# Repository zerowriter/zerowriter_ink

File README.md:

# zerowriter_ink

General repo for all things Zerowriter Ink.

Note that the current public firmware is 1.1. If you are using a factory Zerowriter Ink, you may experience some bugs.

For those field testing or using new units, consider opening an issue if you find bugs. You can do that here: (https://github.com/zerowriter/zerowriter_ink/issues)

This repo will be updated with the source code, documentation, and design files for ZW Ink.

Also consider sharing your custom fonts (.bbf), layouts (layout.json), and other tools you may find helpful.

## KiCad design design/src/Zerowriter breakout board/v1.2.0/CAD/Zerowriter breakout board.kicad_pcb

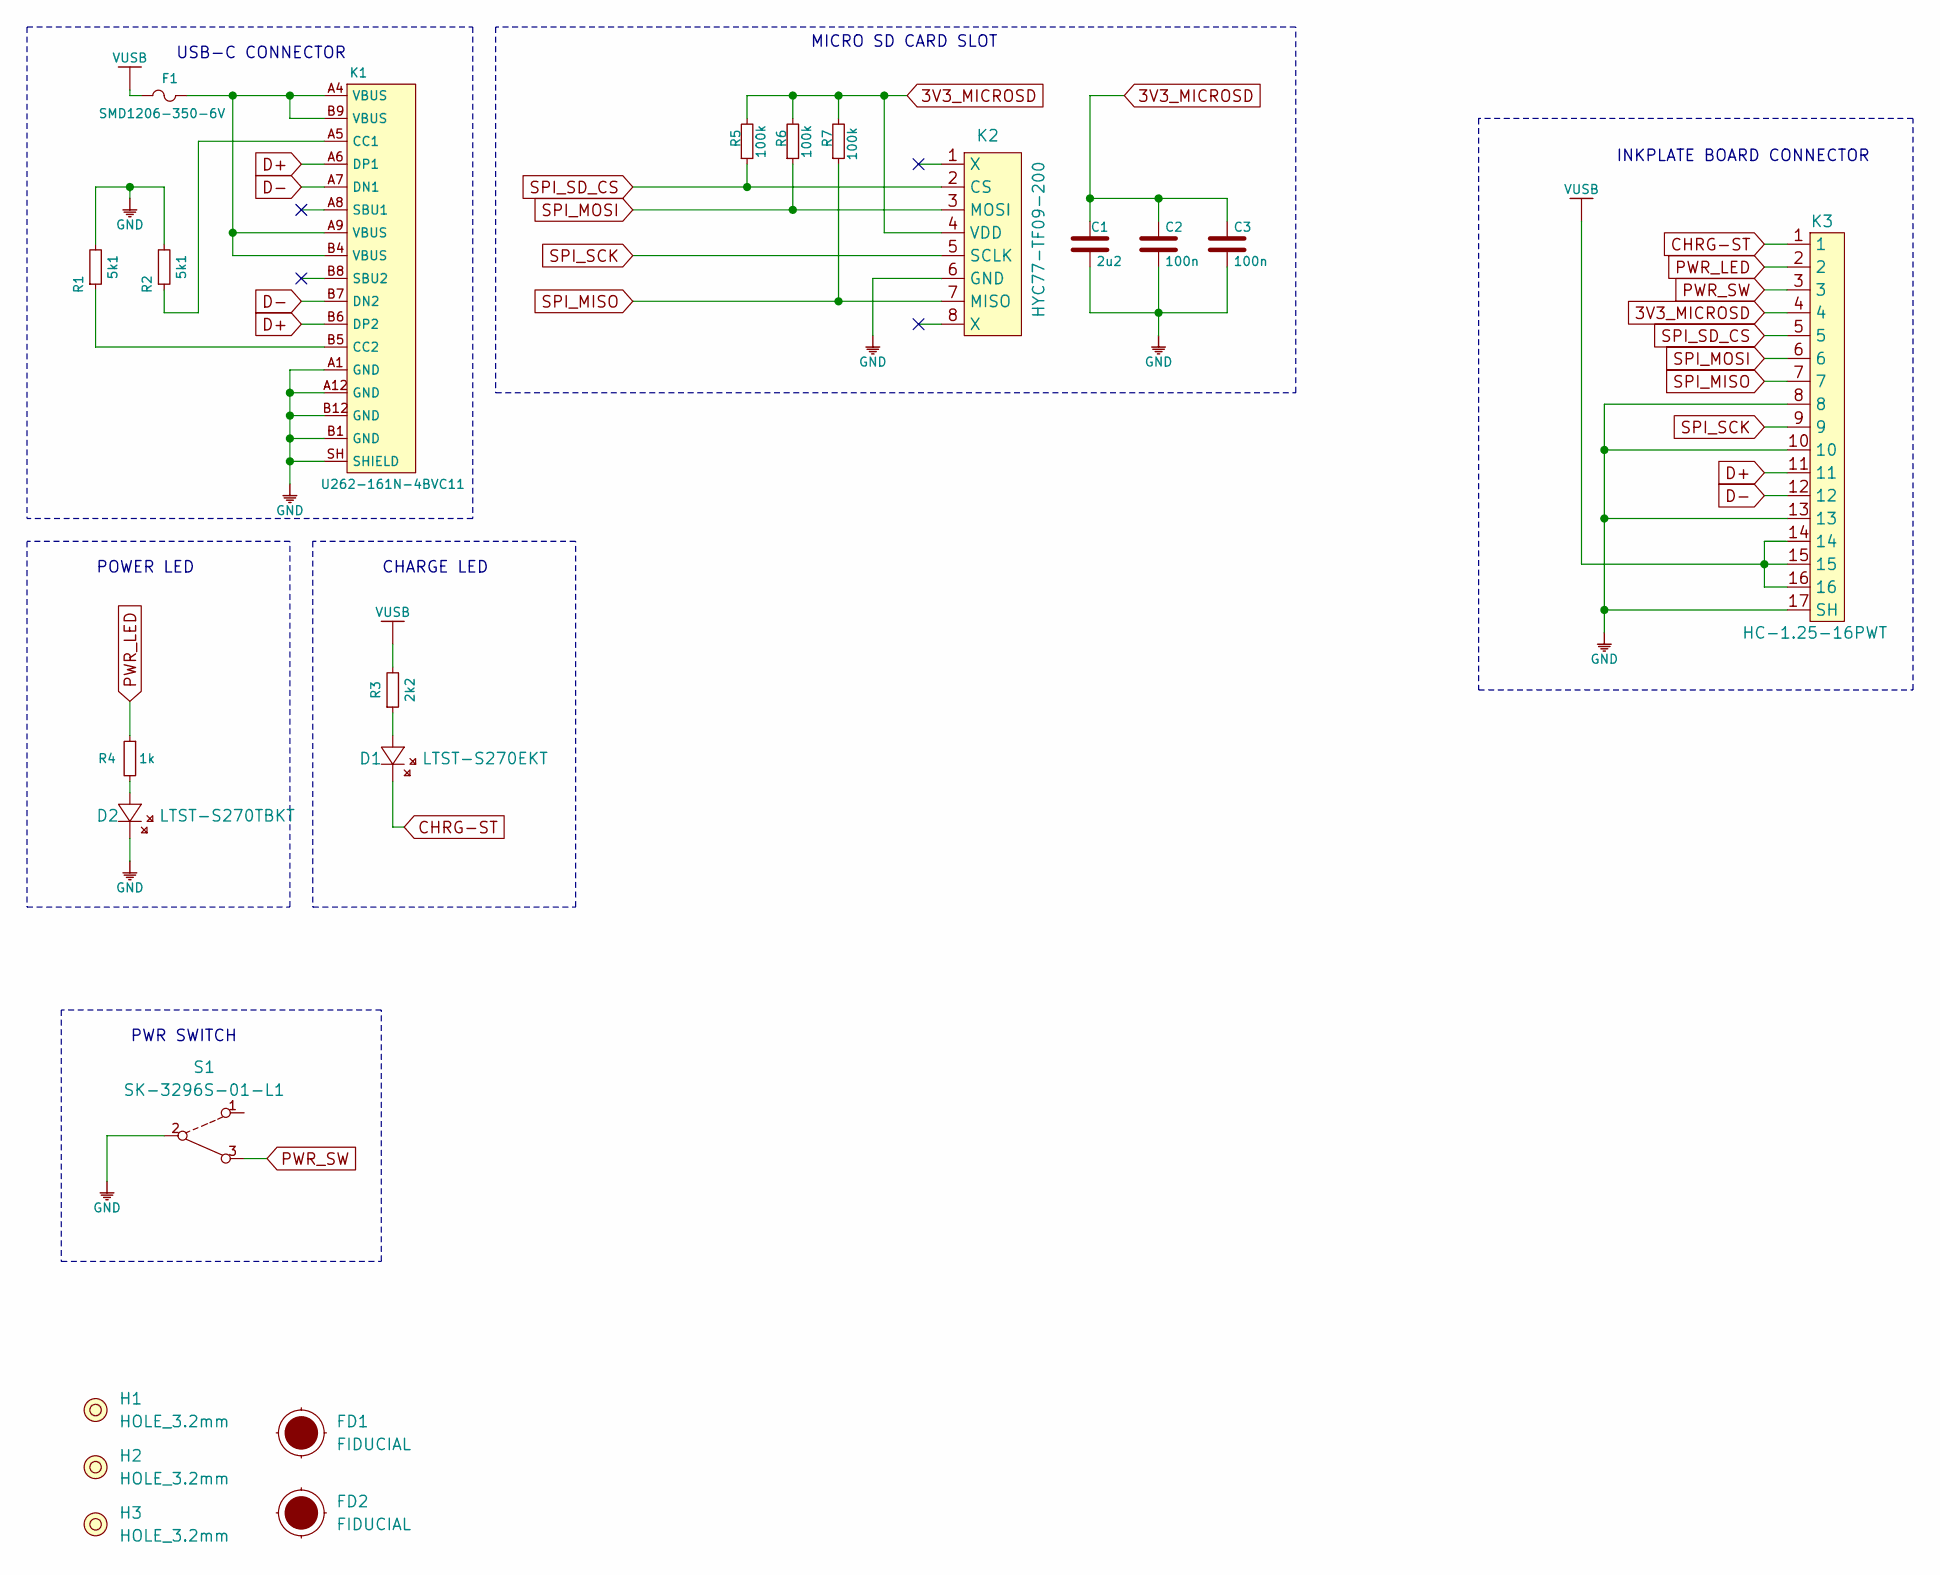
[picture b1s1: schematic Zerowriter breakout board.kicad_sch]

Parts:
C1: 2u2; 0603C
C2, C3: 100n; 0603C
D1: LTST-S270EKT; LTST-S270GKT
D2: LTST-S270TBKT; LTST-S270GKT
F1: SMD1206-350-6V; 1206FUSE
FD1, FD2: FIDUCIAL
H1, H2, H3: HOLE_3.2mm
K1: U262-161N-4BVC11
K2: HYC77-TF09-200
K3: HC-1.25-16PWT
R1, R2: 5k1; 0603R
R3: 2k2; 0603R
R4: 1k; 0603R
R5, R6, R7: 100k; 0603R
S1: SK-3296S-01-L1

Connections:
3V3_MICROSD: C1.2, C2.2, C3.2, K2.4 (VDD), K3.4, R5.2, R6.2, R7.2
CHRG-ST: D1.2 (K), K3.1
D+: K1.A6 (DP1), K1.B6 (DP2), K3.11
D-: K1.A7 (DN1), K1.B7 (DN2), K3.12
GND: C1.1, C2.1, C3.1, D2.2 (K), K1.A1 (GND), K1.A12 (GND), K1.B1 (GND), K1.B12 (GND), K1.SH (SHIELD), K2.6 (GND), K3.8, K3.10, K3.13, K3.17 (SH), R1.2, R2.2, S1.2
unnamed: D1.1 (A), R3.1
unnamed: D2.1 (A), R4.2
unnamed: F1.2, K1.A4 (VBUS), K1.A9 (VBUS), K1.B4 (VBUS), K1.B9 (VBUS)
unnamed: K1.A5 (CC1), R2.1
unnamed: K1.B5 (CC2), R1.1
PWR_LED: K3.2, R4.1
PWR_SW: K3.3, S1.3
SPI_MISO: K2.7 (MISO), K3.7, R7.1
SPI_MOSI: K2.3 (MOSI), K3.6, R6.1
SPI_SCK: K2.5 (SCLK), K3.9
SPI_SD_CS: K2.2 (CS), K3.5, R5.1
VUSB: F1.1, K3.14, K3.15, K3.16, R3.2

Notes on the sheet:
POWER LED
USB-C CONNECTOR
INKPLATE BOARD CONNECTOR
MICRO SD CARD SLOT
PWR SWITCH
CHARGE LED

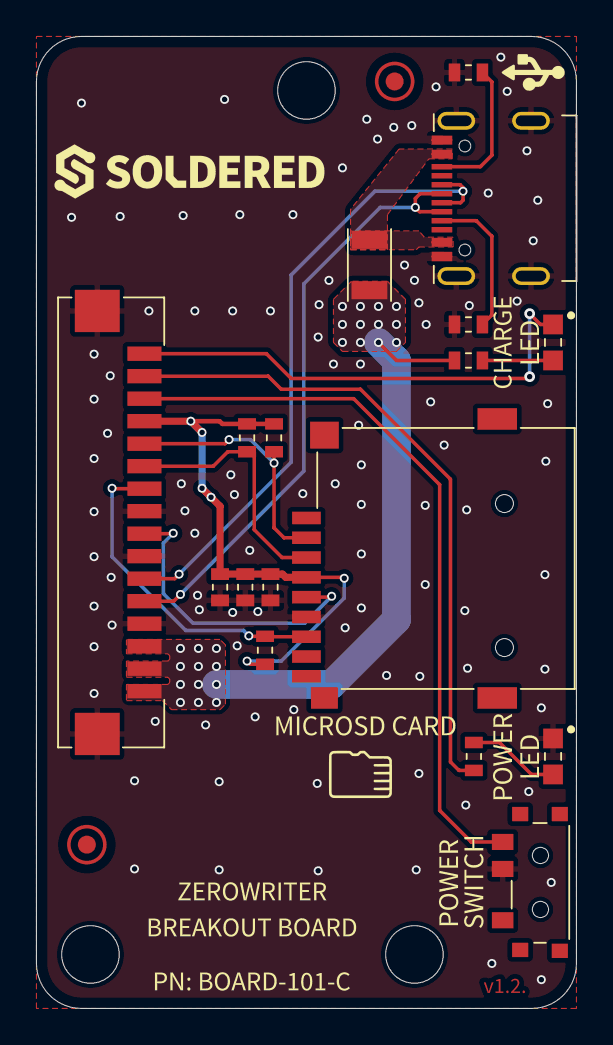
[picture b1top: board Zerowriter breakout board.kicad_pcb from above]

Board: 2 copper layers, 30.0 x 54.0 mm, 32 parts (0 on the bottom side), 17 nets.

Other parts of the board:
kibuzzard-63F8A516: G***; kibuzzard-63F8A516
kibuzzard-63F896F5: G***; kibuzzard-63F896F5
kibuzzard-63F8971E, kibuzzard-63F8971E#2: G***; kibuzzard-63F8971E
kibuzzard-63F89702: G***; kibuzzard-63F89702
kibuzzard-63F89711: G***; kibuzzard-63F89711
kibuzzard-672A36B8: G***; kibuzzard-672A36B8
kibuzzard-672A3648: G***; kibuzzard-672A3648
kibuzzard-672A3655: G***; kibuzzard-672A3655
kibuzzard-68340179: G***; kibuzzard-68340179

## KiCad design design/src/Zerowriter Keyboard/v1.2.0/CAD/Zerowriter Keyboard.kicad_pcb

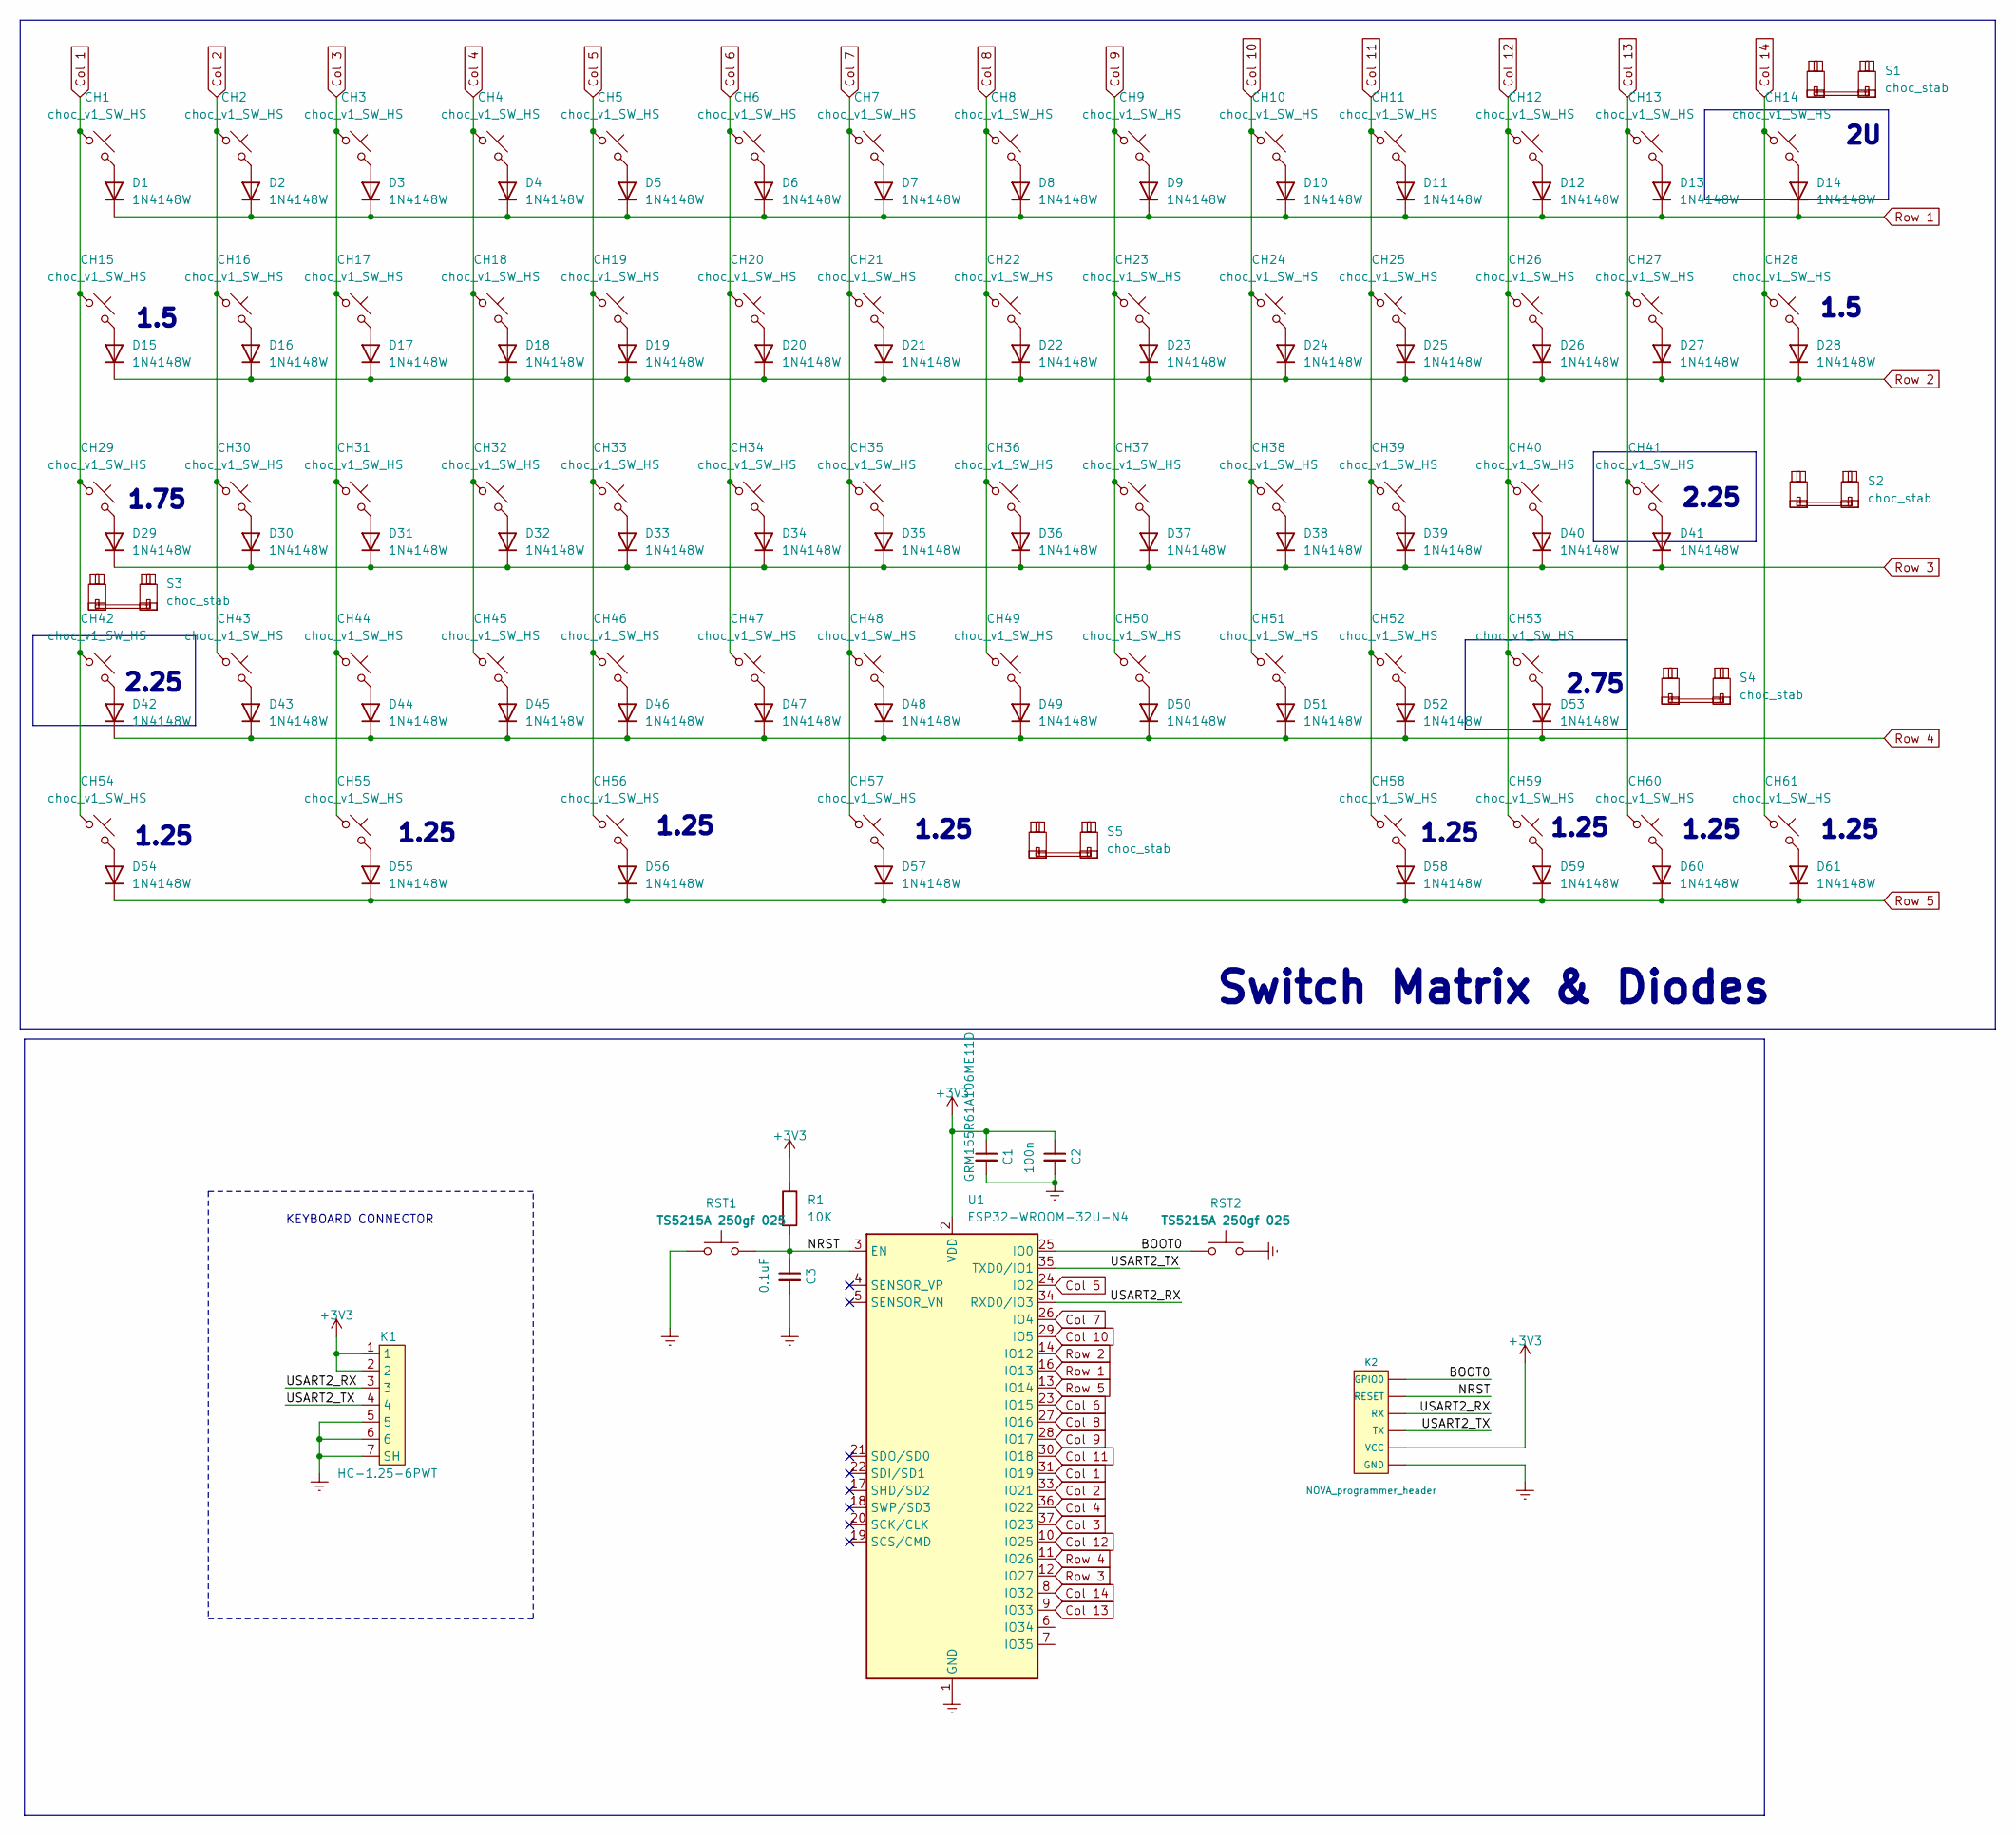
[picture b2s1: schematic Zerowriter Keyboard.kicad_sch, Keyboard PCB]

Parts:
C1: GRM155R61A106ME11D; C_0402_1005Metric_Pad0.74x0.62mm_HandSolder
C2: 100n; C_0402_1005Metric_Pad0.74x0.62mm_HandSolder; JLCPCB part# C1557
C3: 0.1uF; C_0402_1005Metric_Pad0.74x0.62mm_HandSolder; JLCPCB part# C1557
CH1, CH2, CH3, CH4, CH5, CH6, CH7, CH8, CH9, CH10, CH11, CH12, CH13, CH14, CH16, CH17, CH18, CH19, CH20, CH21, CH22, CH23, CH24, CH25, CH26, CH27, CH30, CH31, CH32, CH33, CH34, CH35, CH36, CH37, CH38, CH39, CH40, CH41, CH42, CH43, CH44, CH45, CH46, CH47, CH48, CH49, CH50, CH51, CH52, CH53: choc_v1_SW_HS; SW_choc_v1_HS_CPG135001S30_1u_custom; JLCPCB part# C5333465
CH15, CH28: choc_v1_SW_HS; SW_choc_v1_HS_CPG135001S30_1.5u_custom; JLCPCB part# C5333465
CH29: choc_v1_SW_HS; SW_choc_v1_HS_CPG135001S30_1.75u_custom; JLCPCB part# C5333465
CH54, CH55, CH56, CH57, CH58, CH59, CH60, CH61: choc_v1_SW_HS; SW_choc_v1_HS_CPG135001S30_1.25u_custom; JLCPCB part# C5333465
D1, D2, D3, D4, D5, D6, D7, D8, D9, D10, D11, D12, D13, D14, D15, D16, D17, D18, D19, D20, D21, D22, D23, D24, D25, D26, D27, D28, D29, D30, D31, D32, D33, D34, D35, D36, D37, D38, D39, D40, D41, D42, D43, D44, D45, D46, D47, D48, D49, D50, D51, D52, D53, D54, D55, D56, D57, D58, D59, D60, D61: 1N4148W; D_SOD-123; JLCPCB part# C2099
K1: HC-1.25-6PWT
K2: NOVA_programmer_header; HEADER_MALE_6X1
R1: 10K; R_0603_1608Metric; JLCPCB part# C25804
RST1, RST2: TS5215A 250gf 025; SW_SPST_SKQG_WithStem; JLCPCB part# C5140332
S1, S2, S3, S4: choc_stab; STAB_choc_2u; JLCPCB part# DNP
S5: choc_stab; Choc-6.25u-cutout; JLCPCB part# DNP
U1: ESP32-WROOM-32U-N4; ESP32-WROOM-32U; JLCPCB part# C328062

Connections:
+3V3: C1.1, C2.1, K1.1, K1.2, K2.2 (VCC), R1.1, U1.2 (VDD)
/BOOT0: K2.6 (GPIO0), RST2.1, U1.25 (IO0)
/NRST: C3.1, K2.5 (RESET), R1.2, RST1.2, U1.3 (EN)
/USART2_RX: K1.3, K2.4 (RX), U1.34 (RXD0/IO3)
/USART2_TX: K1.4, K2.3 (TX), U1.35 (TXD0/IO1)
Col 1: CH1.1, CH15.1, CH29.1, CH42.1, CH54.1, U1.31 (IO19)
Col 2: CH2.1, CH16.1, CH30.1, CH43.1, U1.33 (IO21)
Col 3: CH3.1, CH17.1, CH31.1, CH44.1, CH55.1, U1.37 (IO23)
Col 4: CH4.1, CH18.1, CH32.1, CH45.1, U1.36 (IO22)
Col 5: CH5.1, CH19.1, CH33.1, CH46.1, CH56.1, U1.24 (IO2)
Col 6: CH6.1, CH20.1, CH34.1, CH47.1, U1.23 (IO15)
Col 7: CH7.1, CH21.1, CH35.1, CH48.1, CH57.1, U1.26 (IO4)
Col 8: CH8.1, CH22.1, CH36.1, CH49.1, U1.27 (IO16)
Col 9: CH9.1, CH23.1, CH37.1, CH50.1, U1.28 (IO17)
Col 10: CH10.1, CH24.1, CH38.1, CH51.1, U1.29 (IO5)
Col 11: CH11.1, CH25.1, CH39.1, CH52.1, CH58.1, U1.30 (IO18)
Col 12: CH12.1, CH26.1, CH40.1, CH53.1, CH59.1, U1.10 (IO25)
Col 13: CH13.1, CH27.1, CH41.1, CH60.1, U1.9 (IO33)
Col 14: CH14.1, CH28.1, CH61.1, U1.8 (IO32)
Earth: C1.2, C2.2, C3.2, K1.5, K1.6, K1.7 (SH), K2.1 (GND), RST1.1, RST2.2, U1.1 (GND), U1.15 (GND), U1.38 (GND), U1.39 (GND)
unnamed: CH1.2, D1.2 (A)
unnamed: CH2.2, D2.2 (A)
unnamed: CH3.2, D3.2 (A)
unnamed: CH4.2, D4.2 (A)
unnamed: CH5.2, D5.2 (A)
unnamed: CH6.2, D6.2 (A)
unnamed: CH7.2, D7.2 (A)
unnamed: CH8.2, D8.2 (A)
unnamed: CH9.2, D9.2 (A)
unnamed: CH10.2, D10.2 (A)
unnamed: CH11.2, D11.2 (A)
unnamed: CH12.2, D12.2 (A)
unnamed: CH13.2, D13.2 (A)
unnamed: CH14.2, D14.2 (A)
unnamed: CH15.2, D15.2 (A)
unnamed: CH16.2, D16.2 (A)
unnamed: CH17.2, D17.2 (A)
unnamed: CH18.2, D18.2 (A)
unnamed: CH19.2, D19.2 (A)
unnamed: CH20.2, D20.2 (A)
unnamed: CH21.2, D21.2 (A)
unnamed: CH22.2, D22.2 (A)
unnamed: CH23.2, D23.2 (A)
unnamed: CH24.2, D24.2 (A)
unnamed: CH25.2, D25.2 (A)
unnamed: CH26.2, D26.2 (A)
unnamed: CH27.2, D27.2 (A)
unnamed: CH28.2, D28.2 (A)
unnamed: CH29.2, D29.2 (A)
unnamed: CH30.2, D30.2 (A)
unnamed: CH31.2, D31.2 (A)
unnamed: CH32.2, D32.2 (A)
unnamed: CH33.2, D33.2 (A)
unnamed: CH34.2, D34.2 (A)
unnamed: CH35.2, D35.2 (A)
unnamed: CH36.2, D36.2 (A)
unnamed: CH37.2, D37.2 (A)
unnamed: CH38.2, D38.2 (A)
unnamed: CH39.2, D39.2 (A)
unnamed: CH40.2, D40.2 (A)
unnamed: CH41.2, D41.2 (A)
unnamed: CH42.2, D42.2 (A)
unnamed: CH43.2, D43.2 (A)
unnamed: CH44.2, D44.2 (A)
unnamed: CH45.2, D45.2 (A)
unnamed: CH46.2, D46.2 (A)
unnamed: CH47.2, D47.2 (A)
unnamed: CH48.2, D48.2 (A)
unnamed: CH49.2, D49.2 (A)
unnamed: CH50.2, D50.2 (A)
unnamed: CH51.2, D51.2 (A)
unnamed: CH52.2, D52.2 (A)
unnamed: CH53.2, D53.2 (A)
unnamed: CH54.2, D54.2 (A)
unnamed: CH55.2, D55.2 (A)
unnamed: CH56.2, D56.2 (A)
unnamed: CH57.2, D57.2 (A)
unnamed: CH58.2, D58.2 (A)
unnamed: CH59.2, D59.2 (A)
unnamed: CH60.2, D60.2 (A)
unnamed: CH61.2, D61.2 (A)
Row 1: D1.1 (K), D2.1 (K), D3.1 (K), D4.1 (K), D5.1 (K), D6.1 (K), D7.1 (K), D8.1 (K), D9.1 (K), D10.1 (K), D11.1 (K), D12.1 (K), D13.1 (K), D14.1 (K), U1.16 (IO13)
Row 2: D15.1 (K), D16.1 (K), D17.1 (K), D18.1 (K), D19.1 (K), D20.1 (K), D21.1 (K), D22.1 (K), D23.1 (K), D24.1 (K), D25.1 (K), D26.1 (K), D27.1 (K), D28.1 (K), U1.14 (IO12)
Row 3: D29.1 (K), D30.1 (K), D31.1 (K), D32.1 (K), D33.1 (K), D34.1 (K), D35.1 (K), D36.1 (K), D37.1 (K), D38.1 (K), D39.1 (K), D40.1 (K), D41.1 (K), U1.12 (IO27)
Row 4: D42.1 (K), D43.1 (K), D44.1 (K), D45.1 (K), D46.1 (K), D47.1 (K), D48.1 (K), D49.1 (K), D50.1 (K), D51.1 (K), D52.1 (K), D53.1 (K), U1.11 (IO26)
Row 5: D54.1 (K), D55.1 (K), D56.1 (K), D57.1 (K), D58.1 (K), D59.1 (K), D60.1 (K), D61.1 (K), U1.13 (IO14)

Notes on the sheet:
1.25
KEYBOARD CONNECTOR
2.75
2.25
Switch Matrix & Diodes
1.5
1.75
1.5

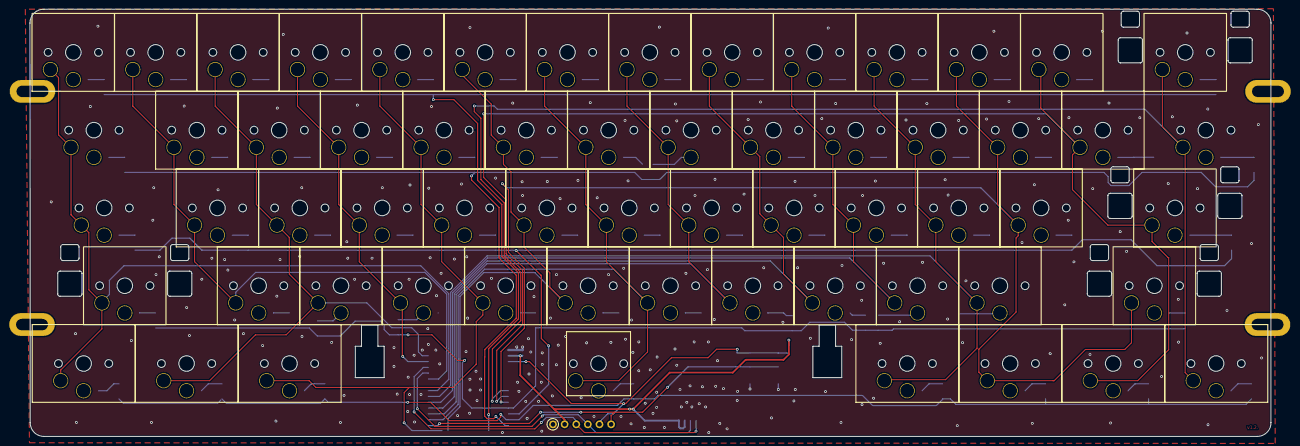
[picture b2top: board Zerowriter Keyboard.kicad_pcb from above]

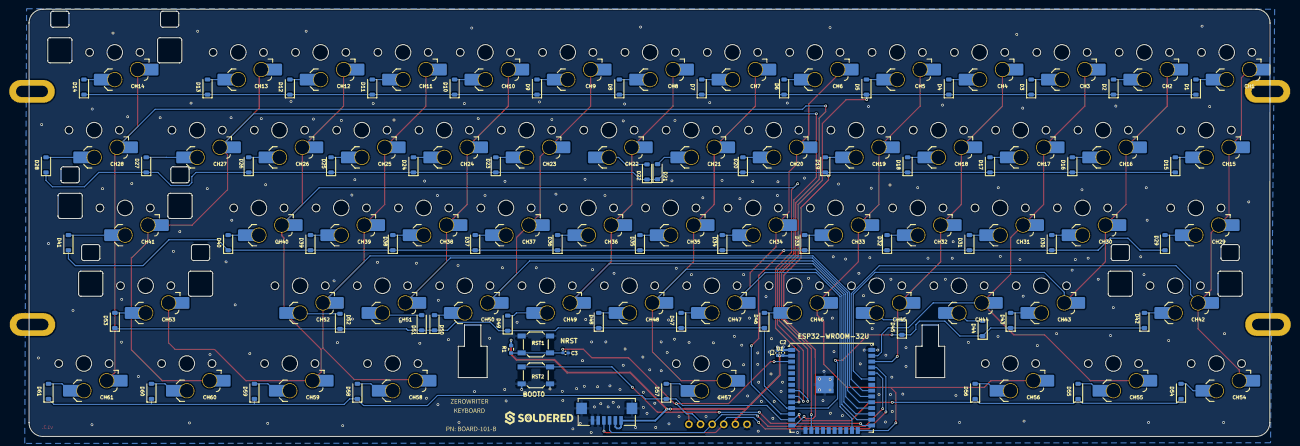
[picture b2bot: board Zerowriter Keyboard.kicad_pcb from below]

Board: 2 copper layers, 271.2 x 93.3 mm, 139 parts (138 on the bottom side), 86 nets.

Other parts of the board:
kibuzzard-672A3648: G***; kibuzzard-672A3648
kibuzzard-6833FF6D: G***; kibuzzard-6833FF6D
kibuzzard-6833FF66: G***; kibuzzard-6833FF66

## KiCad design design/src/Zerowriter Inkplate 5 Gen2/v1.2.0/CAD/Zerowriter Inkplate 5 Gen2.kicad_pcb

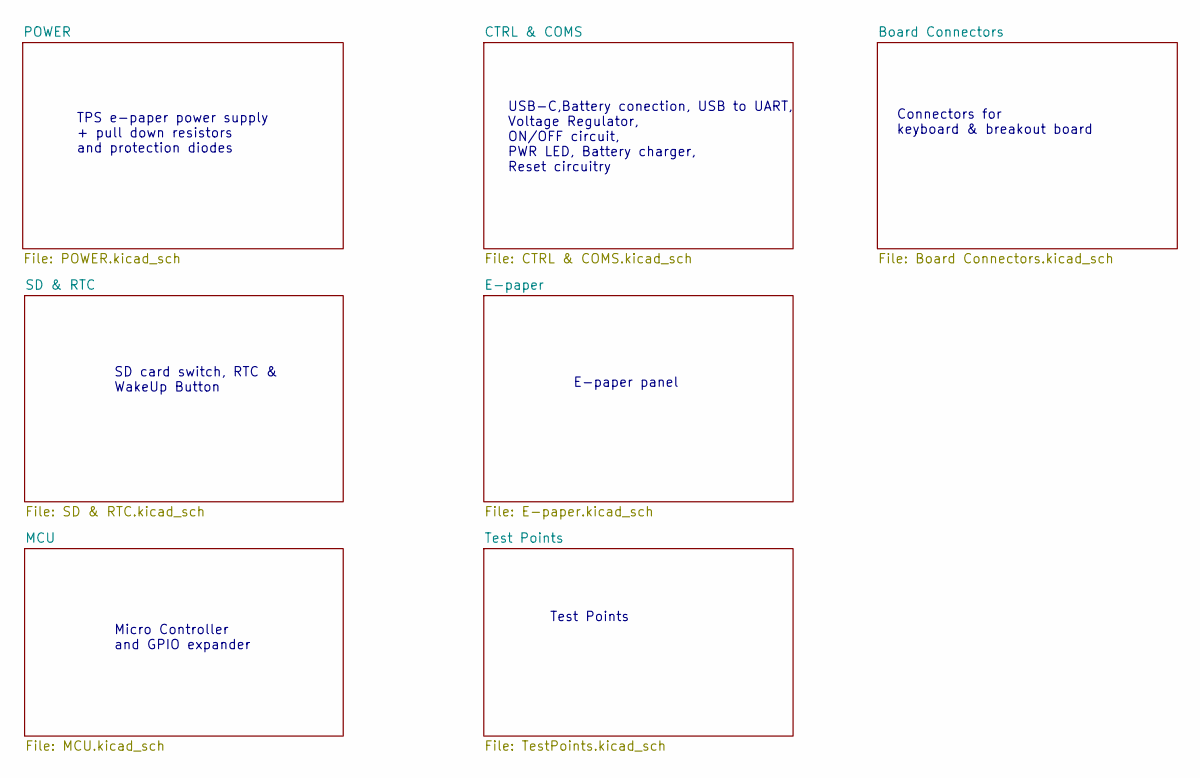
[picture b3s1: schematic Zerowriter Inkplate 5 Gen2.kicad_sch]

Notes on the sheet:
Test Points
USB-C,Battery conection, USB to UART, Voltage Regulator, ON/OFF circuit, PWR LED, Battery charger, Reset circuitry
SD card switch, RTC & WakeUp Button
Micro Controller and GPIO expander
TPS e-paper power supply + pull down resistors and protection diodes
Connectors for keyboard & breakout board
E-paper panel

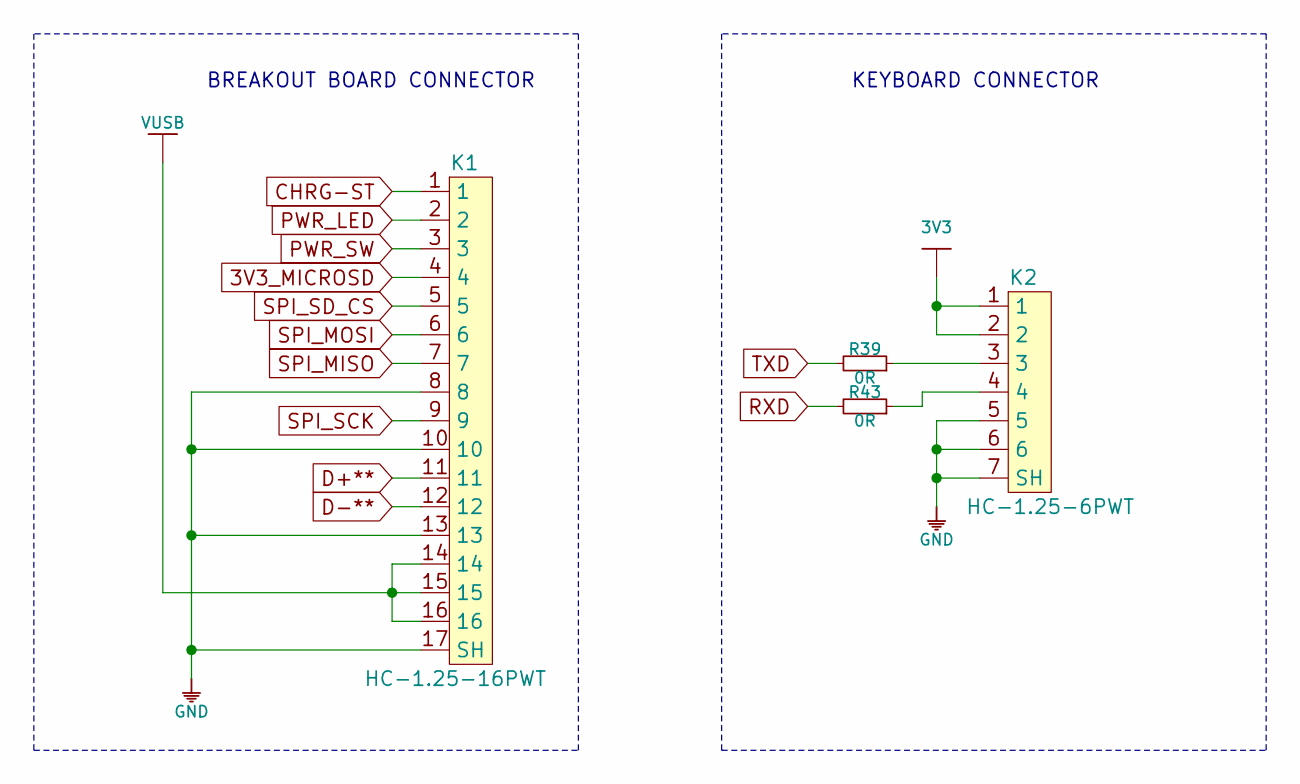
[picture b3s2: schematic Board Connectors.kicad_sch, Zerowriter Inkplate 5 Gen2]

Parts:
K1: HC-1.25-16PWT
K2: HC-1.25-6PWT
R39, R43: 0R; 0603R

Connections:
3V3: K2.1, K2.2; also elsewhere on the board
3V3_MICROSD: K1.4; also elsewhere on the board
CHRG-ST: K1.1; also elsewhere on the board
D+**: K1.11; also elsewhere on the board
D-**: K1.12; also elsewhere on the board
GND: K1.8, K1.10, K1.13, K1.17 (SH), K2.5, K2.6, K2.7 (SH); also elsewhere on the board
unnamed: K2.3, R39.1
unnamed: K2.4, R43.1
PWR_LED: K1.2; also elsewhere on the board
PWR_SW: K1.3; also elsewhere on the board
RXD: R43.2; also elsewhere on the board
SPI_MISO: K1.7; also elsewhere on the board
SPI_MOSI: K1.6; also elsewhere on the board
SPI_SCK: K1.9; also elsewhere on the board
SPI_SD_CS: K1.5; also elsewhere on the board
TXD: R39.2; also elsewhere on the board
VUSB: K1.14, K1.15, K1.16; also elsewhere on the board

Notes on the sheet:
KEYBOARD CONNECTOR
BREAKOUT BOARD CONNECTOR

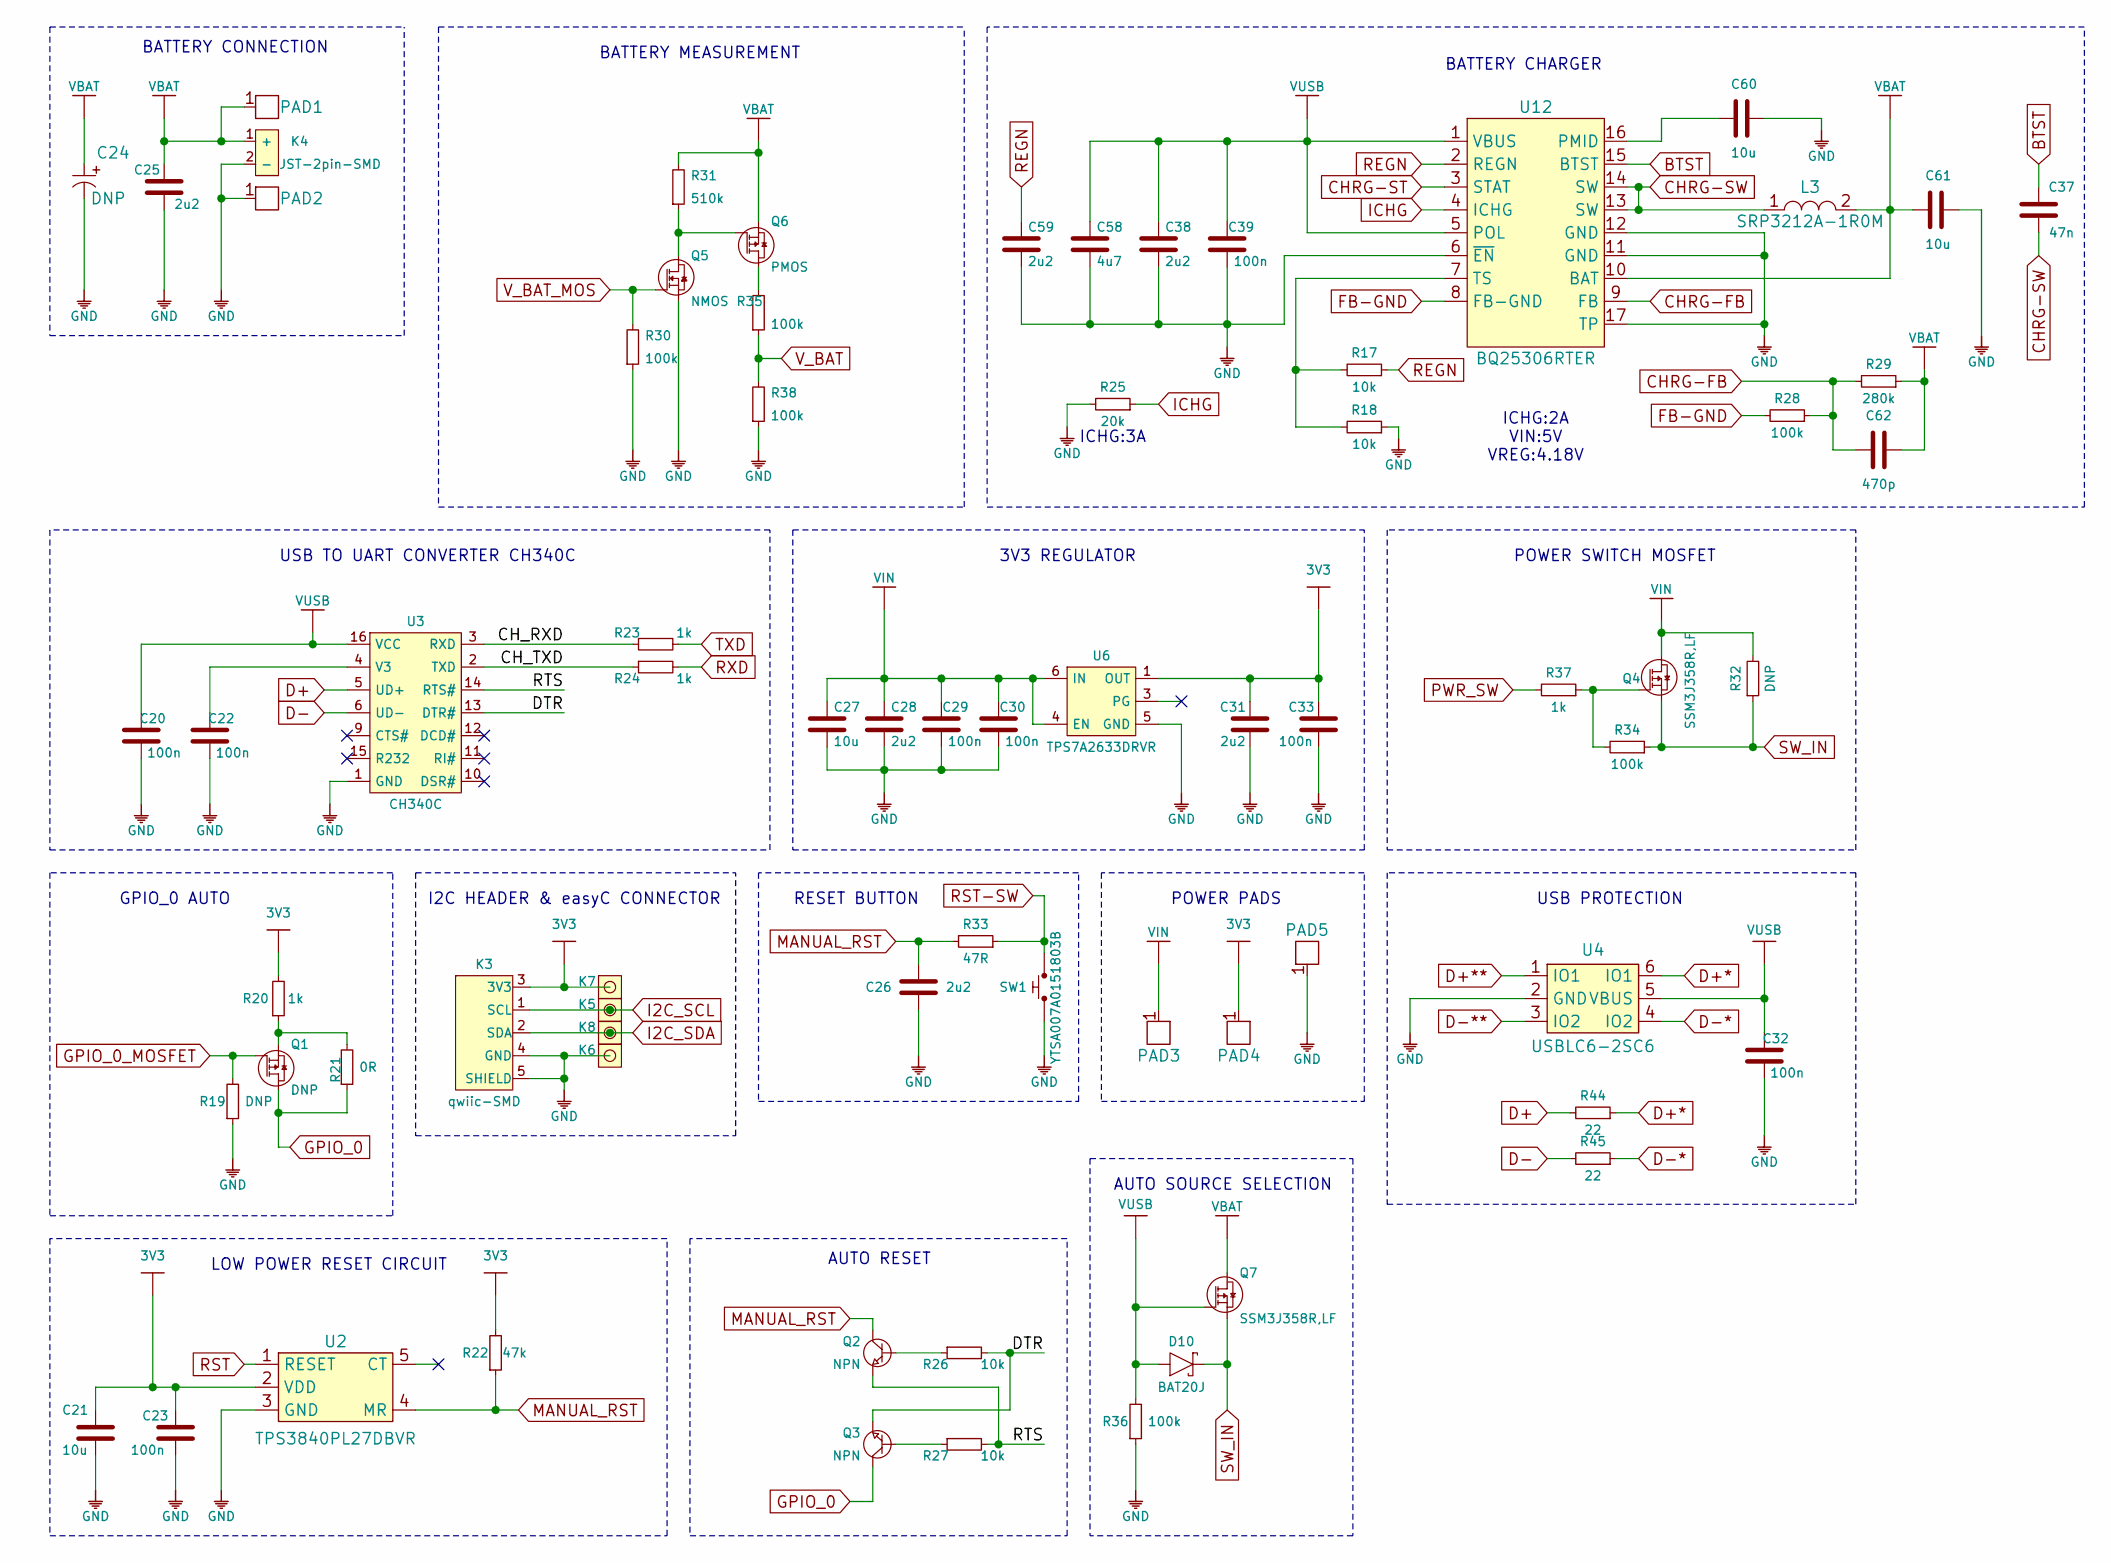
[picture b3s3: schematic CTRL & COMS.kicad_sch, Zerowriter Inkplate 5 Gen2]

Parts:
C20, C22, C23, C29, C30, C32, C33, C39: 100n; 0603C
C21, C27, C60, C61: 10u; 1206C
C24: DNP; 2917C
C25, C26, C28, C31, C38, C59: 2u2; 0603C
C37: 47n; 0603C
C58: 4u7; 0603C
C62: 470p; 0603C
D10: BAT20J; SOD-323
K3: qwiic-SMD; qwiic-connector
K4: JST-2pin-SMD
K5, K6, K7, K8: HEADER_MALE_1X1_Inkplate
L3: SRP3212A-1R0M; SRP3212A
PAD1, PAD2, PAD3, PAD4, PAD5: PAD_4x4
Q1: DNP; SOT-23-3
Q2, Q3: NPN; SOT-23-3
Q4, Q7: SSM3J358R,LF; SOT-23-3
Q5: NMOS; SOT-23-3
Q6: PMOS; SOT-23-3
R17, R18, R26, R27: 10k; 0603R
R19, R32: DNP; 0603R
R20, R23, R24, R37: 1k; 0603R
R21: 0R; 0603R
R22: 47k; 0603R
R25: 20k; 0603R
R28, R30, R34, R35, R36, R38: 100k; 0603R
R29: 280k; 0603R
R31: 510k; 0603R
R33: 47R; 0603R
R44, R45: 22; 0603R
SW1: YTSA007A0151803B
U2: TPS3840PL27DBVR; SOT-23-5
U3: CH340C; SOP-16
U4: USBLC6-2SC6; Sot23-6
U6: TPS7A2633DRVR
U12: BQ25306RTER; WQFN-16

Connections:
3V3: C21.2, C23.2, C31.2, C33.2, K3.3 (3V3), K7.1, PAD4.1, R20.2, R22.2, U2.2 (VDD), U6.1 (OUT); also elsewhere on the board
/CTRL & COMS/CH_RXD: R23.1, U3.3 (RXD)
/CTRL & COMS/CH_TXD: R24.1, U3.2 (TXD)
/CTRL & COMS/DTR: Q3.2 (E), R26.2, U3.13 (DTR#)
/CTRL & COMS/RTS: Q2.2 (E), R27.2, U3.14 (RTS#)
BTST: C37.2, U12.15 (BTST)
CHRG-FB: C62.2, R28.1, R29.2, U12.9 (FB)
CHRG-ST: U12.3 (STAT); also elsewhere on the board
CHRG-SW: C37.1, L3.1, U12.13 (SW), U12.14 (SW)
D+: R44.2, U3.5 (UD+); also elsewhere on the board
D+*: R44.1, U4.6 (IO1)
D+**: U4.1 (IO1); also elsewhere on the board
D-: R45.2, U3.6 (UD-); also elsewhere on the board
D-*: R45.1, U4.4 (IO2)
D-**: U4.3 (IO2); also elsewhere on the board
FB-GND: R28.2, U12.8 (FB-GND)
GND: C20.1, C21.1, C22.1, C23.1, C24.2 (-), C25.1, C26.1, C27.1, C28.1, C29.1, C30.1, C31.1, C32.1, C33.1, C38.1, C39.1, C58.1, C59.1, C60.1, C61.1, K3.4 (GND), K3.5 (SHIELD), K4.2 (-), K6.1, PAD2.1, PAD5.1, Q5.2 (S), R18.1, R19.1, R25.2, R30.1, R36.1, R38.1, SW1.1, U2.3 (GND), U3.1 (GND), U4.2 (GND), U6.5 (GND), U12.6 (~EN), U12.11 (GND), U12.12 (GND), U12.17 (TP); also elsewhere on the board
GPIO_0: Q1.3 (D), Q3.3 (C), R21.1; also elsewhere on the board
GPIO_0_MOSFET: Q1.1 (G), R19.2; also elsewhere on the board
I2C_SCL: K3.1 (SCL), K5.1; also elsewhere on the board
I2C_SDA: K3.2 (SDA), K8.1; also elsewhere on the board
ICHG: R25.1, U12.4 (ICHG)
MANUAL_RST: C26.2, Q2.3 (C), R22.1, R33.2, U2.4 (MR); also elsewhere on the board
unnamed: Q1.2 (S), R20.1, R21.2
unnamed: Q2.1 (B), R26.1
unnamed: Q3.1 (B), R27.1
unnamed: Q4.1 (G), R34.2, R37.1
unnamed: Q5.3 (D), Q6.1 (G), R31.1
unnamed: Q6.3 (D), R35.2
unnamed: C22.2, U3.4 (V3)
unnamed: C60.2, U12.16 (PMID)
unnamed: R17.2, R18.2, U12.7 (TS)
PWR_SW: R37.2; also elsewhere on the board
REGN: C59.2, R17.1, U12.2 (REGN)
RST: U2.1 (RESET); also elsewhere on the board
RST-SW: R33.1, SW1.2; also elsewhere on the board
RXD: R24.2; also elsewhere on the board
SW_IN: D10.2 (C), Q4.2 (S), Q7.2 (S), R32.1, R34.1; also elsewhere on the board
TXD: R23.2; also elsewhere on the board
VBAT: C24.1 (+), C25.2, C61.2, C62.1, K4.1 (+), L3.2, PAD1.1, Q6.2 (S), Q7.3 (D), R29.1, R31.2, U12.10 (BAT); also elsewhere on the board
VIN: C27.2, C28.2, C29.2, C30.2, PAD3.1, Q4.3 (D), R32.2, U6.4 (EN), U6.6 (IN); also elsewhere on the board
VUSB: C20.2, C32.2, C38.2, C39.2, C58.2, D10.1 (A), Q7.1 (G), R36.2, U3.16 (VCC), U4.5 (VBUS), U12.1 (VBUS), U12.5 (POL); also elsewhere on the board
V_BAT: R35.1, R38.2; also elsewhere on the board
V_BAT_MOS: Q5.1 (G), R30.2; also elsewhere on the board

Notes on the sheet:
LOW POWER RESET CIRCUIT
USB PROTECTION
AUTO RESET
GPIO_0 AUTO
ICHG:3A
AUTO SOURCE SELECTION
RESET BUTTON
POWER SWITCH MOSFET
I2C HEADER & easyC CONNECTOR
USB TO UART CONVERTER CH340C
BATTERY CHARGER
BATTERY CONNECTION
ICHG:2A VIN:5V VREG:4.18V
3V3 REGULATOR
BATTERY MEASUREMENT
POWER PADS
